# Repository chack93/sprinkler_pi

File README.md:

# sprinkler_pi

Raspberry Pi controlled plant sprinkler.

## files

### sprinkler_pi

contains pump & sensor controller.

### sprinkler_pi_ui

is a phoenix server providing a website to control the sprinkler system.

### hardware

contains the kicad project of the used circuit.
led's, manual override button & water level sensor are supplied by the raspberry (3.3V).  
pump & solenoid powered valve need to be powered by an external 12V power supply. the power supply need to be powerful enought to support both water pump & solenoid, as well as momentary inrush current on power on.  
most water pump can't pump air well, therefore a solenoid valve is attached right after the pump output to stop backflow. the valve need to be normally closed for this to work.

## building
```
cd sprinkler_pi

# specify raspberry model (raspberry zero in this case)
export MIX_TARGET=rpi0

# setup wifi to connect to
export NERVES_NETWORK_KEY_MGMT=WPA-PSK
export NERVES_NETWORK_SSID=INSERT_WIFI
export NERVES_NETWORK_PSK=INSERT_WIFI_PW

# fetch dependencies
mix deps.get

# generate secret key base for phoenix
mix phx.gen.secret
# copy & paste generated secret
export SECRET_KEY_BASE=INSERT_SKB

# generate image & burn on attached sd-card
MIX_ENV=prod mix firmware.burn
```

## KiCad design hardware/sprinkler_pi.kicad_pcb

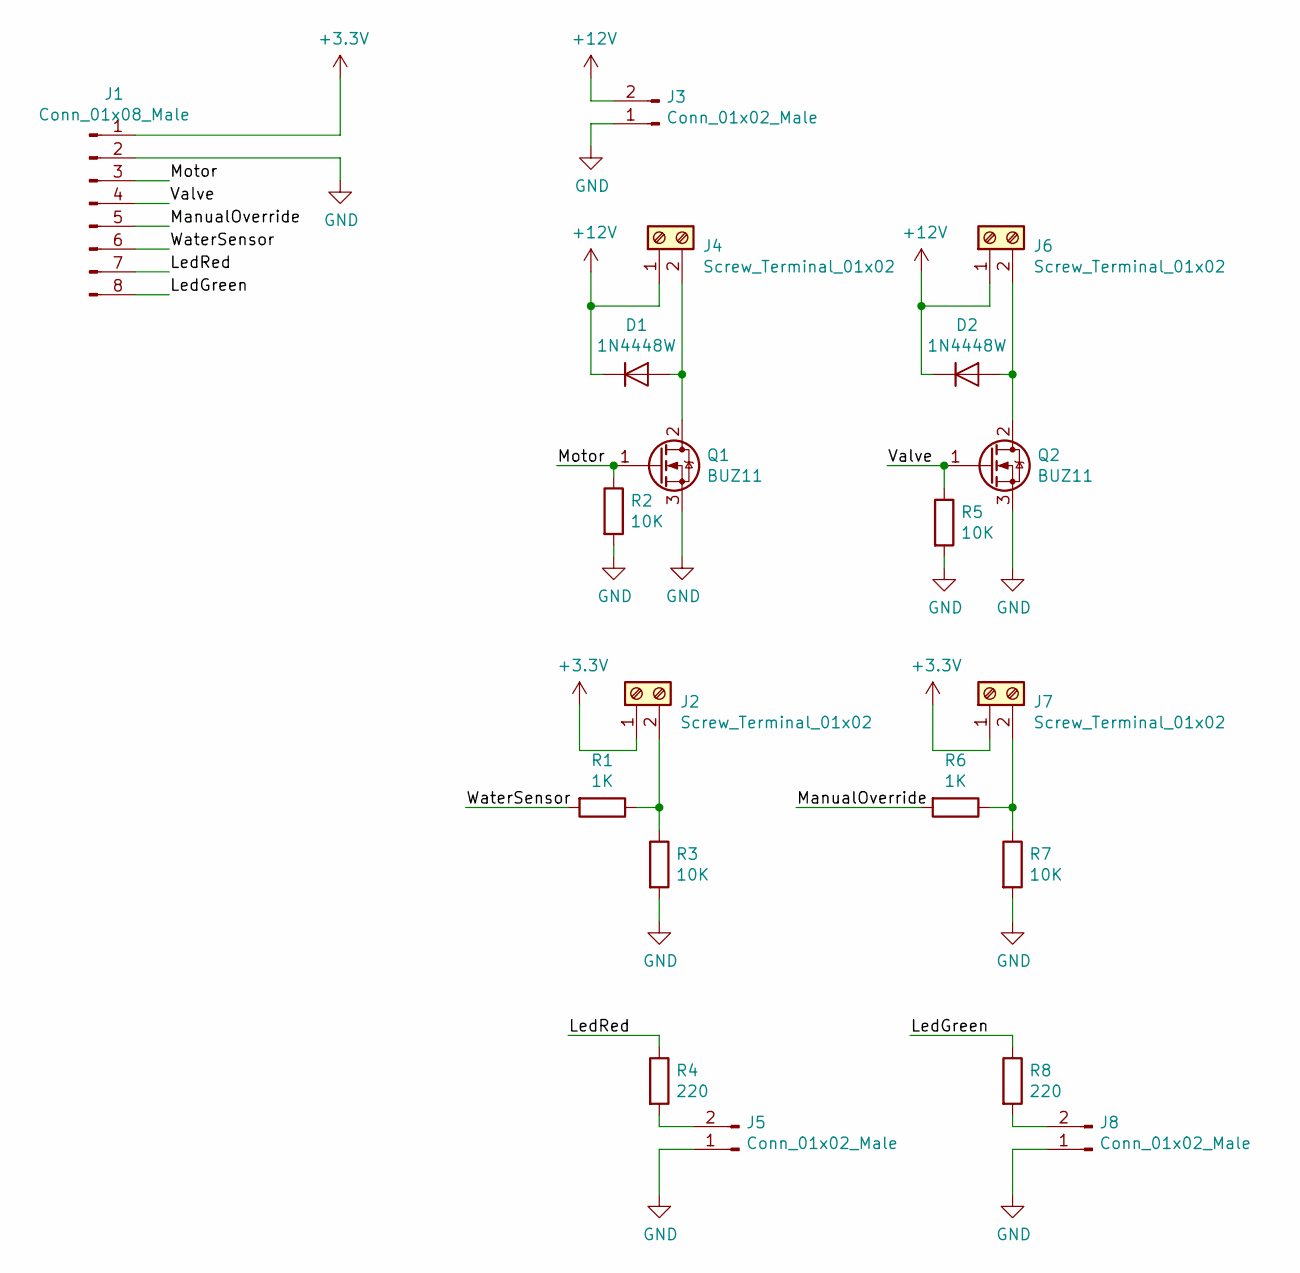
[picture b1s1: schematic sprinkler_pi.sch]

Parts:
D1, D2: 1N4448W; D_SOD-123
J1: Conn_01x08_Male; PinHeader_1x08_P2.54mm_Vertical
J2, J4, J6, J7: Screw_Terminal_01x02; TerminalBlock_bornier-2_P5.08mm
J3, J5, J8: Conn_01x02_Male; PinHeader_1x02_P2.54mm_Vertical
Q1, Q2: BUZ11; TO-220-3_Vertical
R1, R6: 1K; R_1206_3216Metric_Pad1.42x1.75mm_HandSolder
R2, R3, R5, R7: 10K; R_1206_3216Metric_Pad1.42x1.75mm_HandSolder
R4, R8: 220; R_1206_3216Metric_Pad1.42x1.75mm_HandSolder

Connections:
+3V3: J1.1, J2.1, J7.1
+12V: D1.1 (K), D2.1 (K), J3.2, J4.1, J6.1
/LedGreen: J1.8, R8.1
/LedRed: J1.7, R4.1
/ManualOverride: J1.5, R6.2
/Motor: J1.3, Q1.1 (G), R2.1
/Valve: J1.4, Q2.1 (G), R5.1
/WaterSensor: J1.6, R1.2
GND: J1.2, J3.1, J5.1, J8.1, Q1.3 (S), Q2.3 (S), R2.2, R3.2, R5.2, R7.2
unnamed: D1.2 (A), J4.2, Q1.2 (D)
unnamed: D2.2 (A), J6.2, Q2.2 (D)
unnamed: J2.2, R1.1, R3.1
unnamed: J5.2, R4.2
unnamed: J7.2, R6.1, R7.1
unnamed: J8.2, R8.2

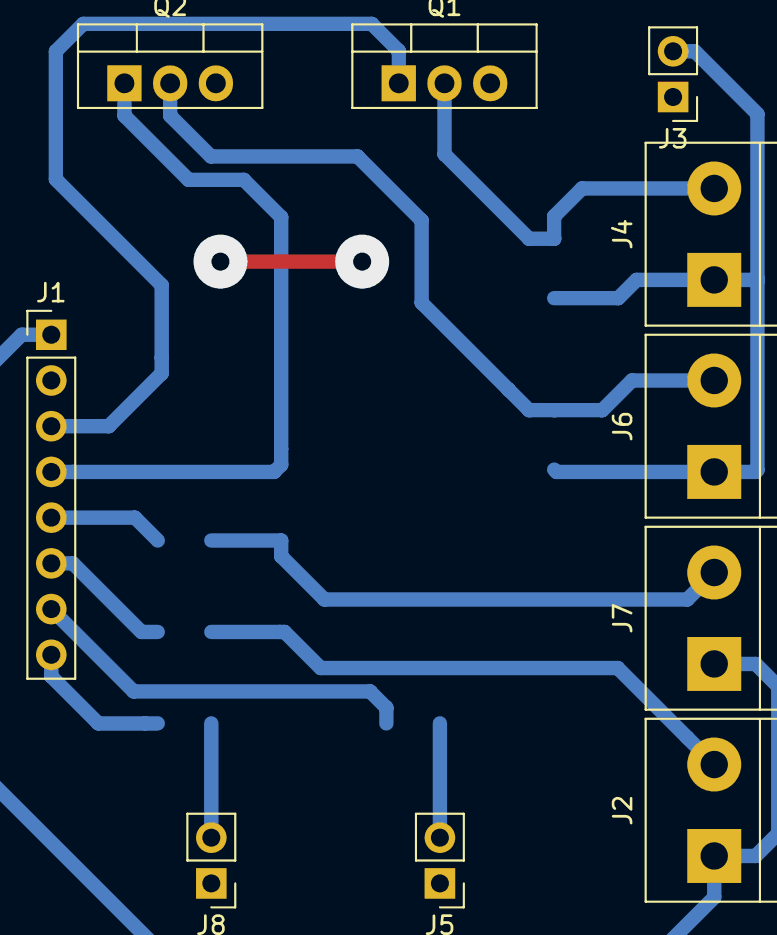
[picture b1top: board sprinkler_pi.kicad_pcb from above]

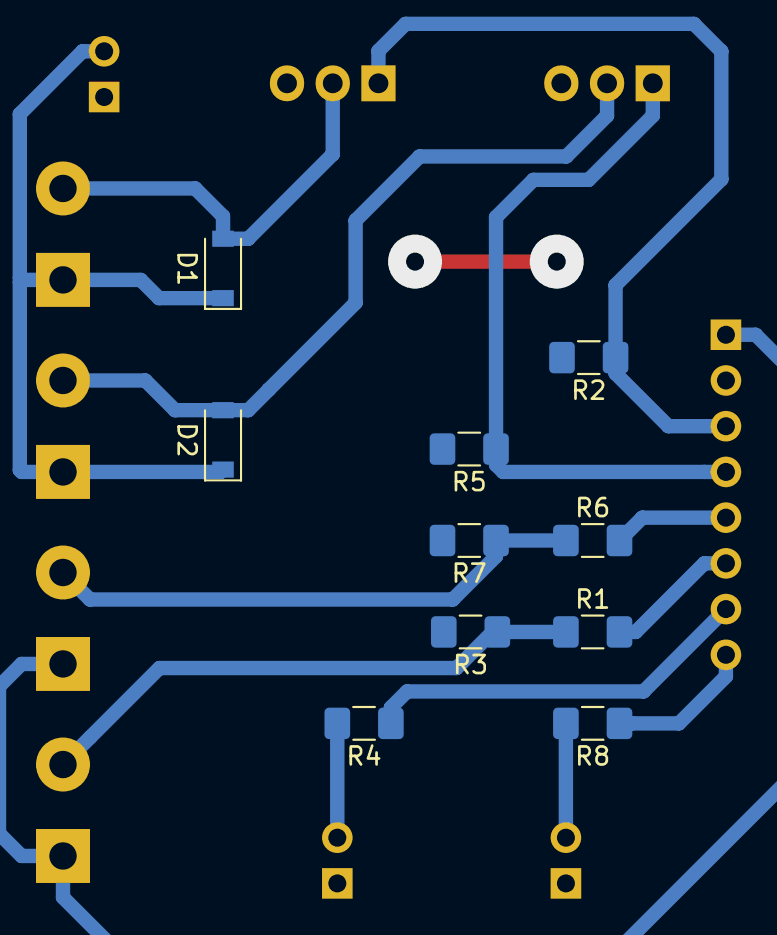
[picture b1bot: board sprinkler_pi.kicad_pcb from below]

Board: 2 copper layers, 20 parts (10 on the bottom side), 15 nets.

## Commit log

2020-02-14 add controller board hardware schematic & pcb design
2020-02-15 add nerves boilerplate
2020-02-16 add phoenix as webserver
2020-02-16 add gpio control genserver
2020-02-17 add easy access functions to Control.ex fix pin assignment
2020-02-22 add dashboard live view
2020-03-01 add schedule & pump control
2020-03-01 fix manual override ui
2020-03-04 add schedule setting ui
2020-03-05 add status message ui
2020-03-05 add setting ui
2020-03-06 fix readme formatting
2020-03-07 add manual override button handler
2020-03-08 fix setting file not written on target
2020-03-08 fix wrong timezone on target fix startup error after adding additional setting
2020-04-05 Bump acorn from 6.4.0 to 6.4.1 in /sprinkler_pi_ui/assets
    Bumps [acorn](https://github.com/acornjs/acorn) from 6.4.0 to 6.4.1.
    - [Release notes](https://github.com/acornjs/acorn/releases)
    - [Commits](https://github.com/acornjs/acorn/compare/6.4.0...6.4.1)
2020-07-19 Bump lodash from 4.17.15 to 4.17.19 in /sprinkler_pi_ui/assets
    Bumps [lodash](https://github.com/lodash/lodash) from 4.17.15 to 4.17.19.
    - [Release notes](https://github.com/lodash/lodash/releases)
    - [Commits](https://github.com/lodash/lodash/compare/4.17.15...4.17.19)
2020-08-01 Bump elliptic from 6.5.2 to 6.5.3 in /sprinkler_pi_ui/assets
    Bumps [elliptic](https://github.com/indutny/elliptic) from 6.5.2 to 6.5.3.
    - [Release notes](https://github.com/indutny/elliptic/releases)
    - [Commits](https://github.com/indutny/elliptic/compare/v6.5.2...v6.5.3)
2020-12-12 Bump ini from 1.3.5 to 1.3.8 in /sprinkler_pi_ui/assets
    Bumps [ini](https://github.com/isaacs/ini) from 1.3.5 to 1.3.8.
    - [Release notes](https://github.com/isaacs/ini/releases)
    - [Commits](https://github.com/isaacs/ini/compare/v1.3.5...v1.3.8)
2021-03-10 Bump elliptic from 6.5.2 to 6.5.4 in /sprinkler_pi_ui/assets
    Bumps [elliptic](https://github.com/indutny/elliptic) from 6.5.2 to 6.5.4.
    - [Release notes](https://github.com/indutny/elliptic/releases)
    - [Commits](https://github.com/indutny/elliptic/compare/v6.5.2...v6.5.4)
2021-03-31 Bump y18n from 3.2.1 to 3.2.2 in /sprinkler_pi_ui/assets
    Bumps [y18n](https://github.com/yargs/y18n) from 3.2.1 to 3.2.2.
    - [Release notes](https://github.com/yargs/y18n/releases)
    - [Changelog](https://github.com/yargs/y18n/blob/master/CHANGELOG.md)
    - [Commits](https://github.com/yargs/y18n/commits)
2021-04-30 Bump ssri from 6.0.1 to 6.0.2 in /sprinkler_pi_ui/assets
    Bumps [ssri](https://github.com/npm/ssri) from 6.0.1 to 6.0.2.
    - [Release notes](https://github.com/npm/ssri/releases)
    - [Changelog](https://github.com/npm/ssri/blob/v6.0.2/CHANGELOG.md)
    - [Commits](https://github.com/npm/ssri/compare/v6.0.1...v6.0.2)
2021-05-11 Bump lodash from 4.17.15 to 4.17.21 in /sprinkler_pi_ui/assets
    Bumps [lodash](https://github.com/lodash/lodash) from 4.17.15 to 4.17.21.
    - [Release notes](https://github.com/lodash/lodash/releases)
    - [Commits](https://github.com/lodash/lodash/compare/4.17.15...4.17.21)
2021-05-11 Bump hosted-git-info from 2.8.5 to 2.8.9 in /sprinkler_pi_ui/assets
    Bumps [hosted-git-info](https://github.com/npm/hosted-git-info) from 2.8.5 to 2.8.9.
    - [Release notes](https://github.com/npm/hosted-git-info/releases)
    - [Changelog](https://github.com/npm/hosted-git-info/blob/v2.8.9/CHANGELOG.md)
    - [Commits](https://github.com/npm/hosted-git-info/compare/v2.8.5...v2.8.9)
2021-05-26 Bump browserslist from 4.8.7 to 4.16.6 in /sprinkler_pi_ui/assets
    Bumps [browserslist](https://github.com/browserslist/browserslist) from 4.8.7 to 4.16.6.
    - [Release notes](https://github.com/browserslist/browserslist/releases)
    - [Changelog](https://github.com/browserslist/browserslist/blob/main/CHANGELOG.md)
    - [Commits](https://github.com/browserslist/browserslist/compare/4.8.7...4.16.6)
2021-06-16 Bump postcss from 7.0.27 to 7.0.36 in /sprinkler_pi_ui/assets
    Bumps [postcss](https://github.com/postcss/postcss) from 7.0.27 to 7.0.36.
    - [Release notes](https://github.com/postcss/postcss/releases)
    - [Changelog](https://github.com/postcss/postcss/blob/main/CHANGELOG.md)
    - [Commits](https://github.com/postcss/postcss/compare/7.0.27...7.0.36)
    ---
    updated-dependencies:
2021-08-12 Bump path-parse from 1.0.6 to 1.0.7 in /sprinkler_pi_ui/assets
    Bumps [path-parse](https://github.com/jbgutierrez/path-parse) from 1.0.6 to 1.0.7.
    - [Release notes](https://github.com/jbgutierrez/path-parse/releases)
    - [Commits](https://github.com/jbgutierrez/path-parse/commits/v1.0.7)
    ---
    updated-dependencies:
    - dependency-name: path-parse
2022-02-10 Bump node-sass from 4.13.1 to 7.0.0 in /sprinkler_pi_ui/assets
    Bumps [node-sass](https://github.com/sass/node-sass) from 4.13.1 to 7.0.0.
    - [Release notes](https://github.com/sass/node-sass/releases)
    - [Changelog](https://github.com/sass/node-sass/blob/master/CHANGELOG.md)
    - [Commits](https://github.com/sass/node-sass/compare/v4.13.1...v7.0.0)
    ---
    updated-dependencies:
2022-02-13 Bump ajv from 6.11.0 to 6.12.6 in /sprinkler_pi_ui/assets
    Bumps [ajv](https://github.com/ajv-validator/ajv) from 6.11.0 to 6.12.6.
    - [Release notes](https://github.com/ajv-validator/ajv/releases)
    - [Commits](https://github.com/ajv-validator/ajv/compare/v6.11.0...v6.12.6)
    ---
    updated-dependencies:
    - dependency-name: ajv
2022-05-14 add .env to gitignore
2022-07-20 Bump terser from 4.6.3 to 4.8.1 in /sprinkler_pi_ui/assets
    Bumps [terser](https://github.com/terser/terser) from 4.6.3 to 4.8.1.
    - [Release notes](https://github.com/terser/terser/releases)
    - [Changelog](https://github.com/terser/terser/blob/master/CHANGELOG.md)
    - [Commits](https://github.com/terser/terser/commits)
    ---
    updated-dependencies:
2022-11-22 Bump loader-utils and webpack-cli in /sprinkler_pi_ui/assets
    Bumps [loader-utils](https://github.com/webpack/loader-utils) to 1.4.2 and updates ancestor dependency [webpack-cli](https://github.com/webpack/webpack-cli). These dependencies need to be updated tog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
    Updates `loader-utils` from 1.4.0 to 1.4.2
    - [Release notes](https://github.com/webpack/loader-utils/releases)
    - [Changelog](https://github.com/webpack/loader-utils/blob/v1.4.2/CHANGELOG.md)
    - [Commits](https://github.com/webpack/loader-utils/compare/v1.4.0...v1.4.2)
    Updates `webpack-cli` from 3.3.11 to 3.3.12
2022-12-05 Bump decode-uri-component from 0.2.0 to 0.2.2 in /sprinkler_pi_ui/assets
    Bumps [decode-uri-component](https://github.com/SamVerschueren/decode-uri-component) from 0.2.0 to 0.2.2.
    - [Release notes](https://github.com/SamVerschueren/decode-uri-component/releases)
    - [Commits](https://github.com/SamVerschueren/decode-uri-component/compare/v0.2.0...v0.2.2)
    ---
    updated-dependencies:
    - dependency-name: decode-uri-component
2022-12-10 Bump qs from 6.5.2 to 6.5.3 in /sprinkler_pi_ui/assets
    Bumps [qs](https://github.com/ljharb/qs) from 6.5.2 to 6.5.3.
    - [Release notes](https://github.com/ljharb/qs/releases)
    - [Changelog](https://github.com/ljharb/qs/blob/main/CHANGELOG.md)
    - [Commits](https://github.com/ljharb/qs/compare/v6.5.2...v6.5.3)
    ---
    updated-dependencies:
2023-01-05 Bump json5 from 1.0.1 to 1.0.2 in /sprinkler_pi_ui/assets
    Bumps [json5](https://github.com/json5/json5) from 1.0.1 to 1.0.2.
    - [Release notes](https://github.com/json5/json5/releases)
    - [Changelog](https://github.com/json5/json5/blob/main/CHANGELOG.md)
    - [Commits](https://github.com/json5/json5/compare/v1.0.1...v1.0.2)
    ---
    updated-dependencies:
2023-03-02 Bump minimist and mkdirp in /sprinkler_pi_ui/assets
    Bumps [minimist](https://github.com/minimistjs/minimist) and [mkdirp](https://github.com/isaacs/node-mkdirp). These dependencies needed to be updated together.
    Updates `minimist` from 1.2.0 to 1.2.8
    - [Release notes](https://github.com/minimistjs/minimist/releases)
    - [Changelog](https://github.com/minimistjs/minimist/blob/main/CHANGELOG.md)
    - [Commits](https://github.com/minimistjs/minimist/compare/v1.2.0...v1.2.8)
    Updates `mkdirp` from 0.5.1 to 0.5.6
